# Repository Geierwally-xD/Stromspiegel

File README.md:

#LED driver 
Output driver 4 LEDs for scale lighting of models.
Layout and circuit diagram is designed with KiCad. 

4 Konstantstromquellen zum Treiben von LEDs zur Scalebeleuchtung von Modellen.

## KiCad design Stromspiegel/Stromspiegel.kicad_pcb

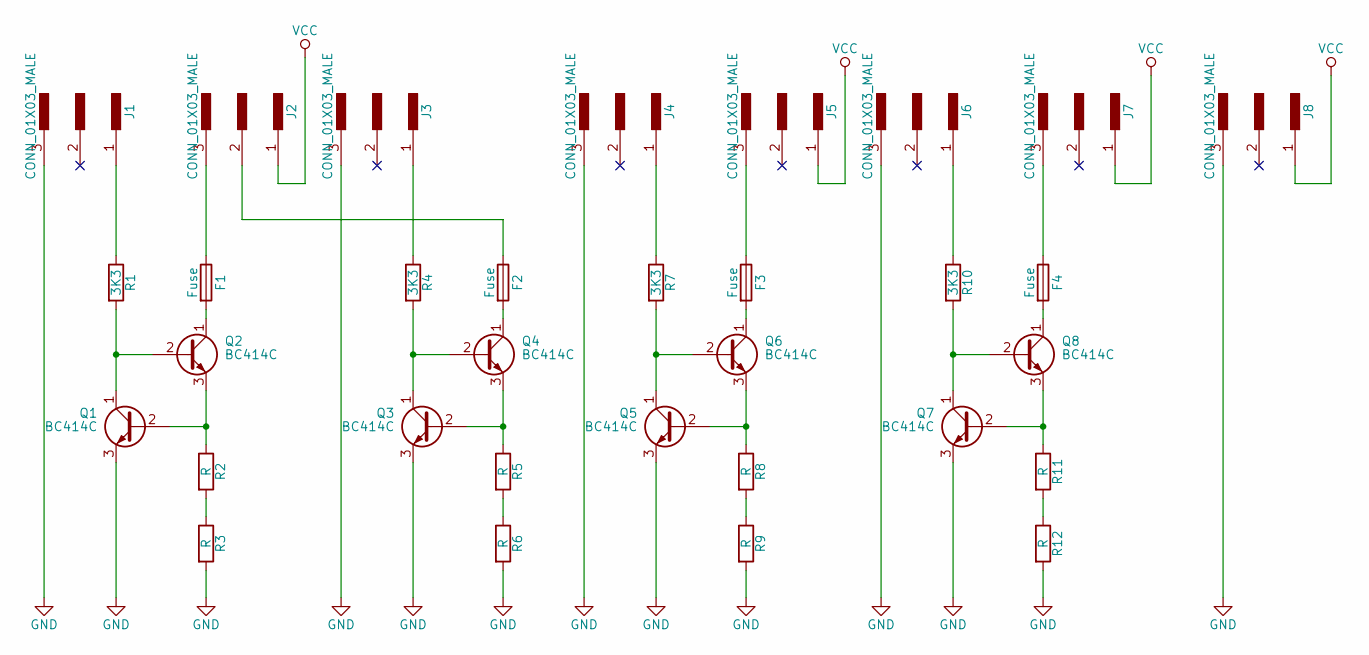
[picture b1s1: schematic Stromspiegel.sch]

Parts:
F1, F2, F3, F4: Fuse; R_Box_L8.4mm_W2.5mm_P5.08mm
J1, J2, J3, J4, J5, J6, J7, J8: CONN_01X03_MALE; Socket_Strip_Straight_1x03_Pitch2.54mm
Q1, Q2, Q3, Q4, Q5, Q6, Q7, Q8: BC414C; TO-92_Molded_Wide
R1, R4, R7, R10: 3K3; R_Axial_DIN0411_L9.9mm_D3.6mm_P15.24mm_Horizontal
R2, R3, R5, R6, R8, R9, R11, R12: R; R_Axial_DIN0411_L9.9mm_D3.6mm_P15.24mm_Horizontal

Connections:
GND: J1.3, J3.3, J4.3, J6.3, J8.3, Q1.3 (E), Q3.3 (E), Q5.3 (E), Q7.3 (E), R3.2, R6.2, R9.2, R12.2
unnamed: F1.1, J2.3
unnamed: F1.2, Q2.1 (C)
unnamed: F2.1, J2.2
unnamed: F2.2, Q4.1 (C)
unnamed: F3.1, J5.3
unnamed: F3.2, Q6.1 (C)
unnamed: F4.1, J7.3
unnamed: F4.2, Q8.1 (C)
unnamed: J1.1, R1.1
unnamed: J3.1, R4.1
unnamed: J4.1, R7.1
unnamed: J6.1, R10.1
unnamed: Q1.1 (C), Q2.2 (B), R1.2
unnamed: Q1.2 (B), Q2.3 (E), R2.1
unnamed: Q3.1 (C), Q4.2 (B), R4.2
unnamed: Q3.2 (B), Q4.3 (E), R5.1
unnamed: Q5.1 (C), Q6.2 (B), R7.2
unnamed: Q5.2 (B), Q6.3 (E), R8.1
unnamed: Q7.1 (C), Q8.2 (B), R10.2
unnamed: Q7.2 (B), Q8.3 (E), R11.1
unnamed: R2.2, R3.1
unnamed: R5.2, R6.1
unnamed: R8.2, R9.1
unnamed: R11.2, R12.1
VCC: J2.1, J5.1, J7.1, J8.1

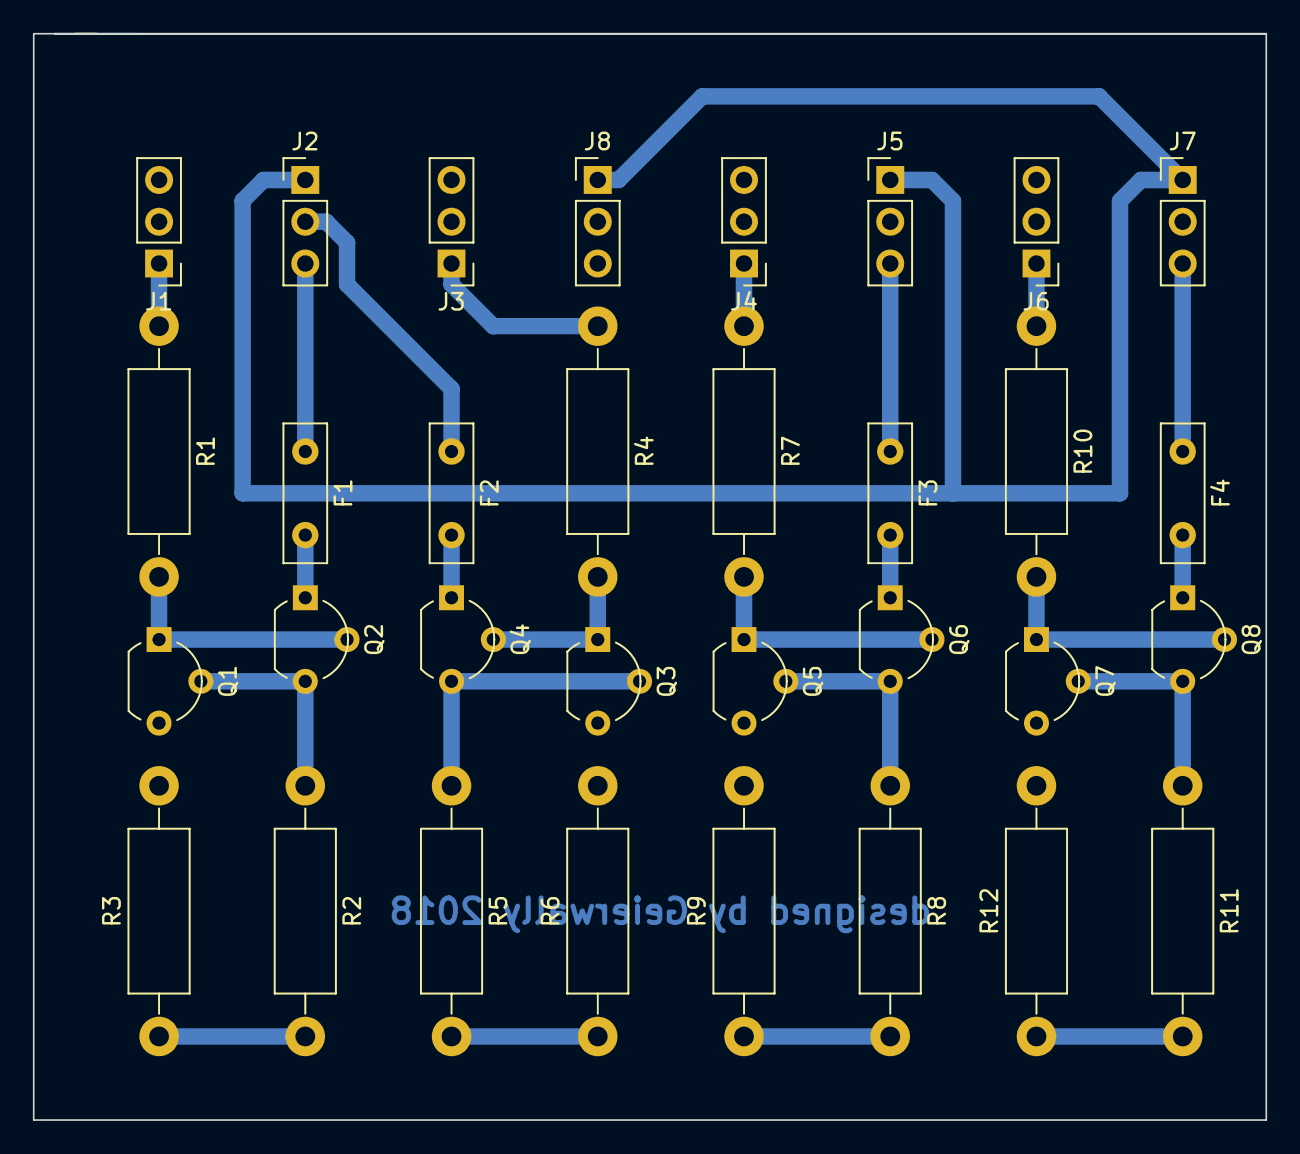
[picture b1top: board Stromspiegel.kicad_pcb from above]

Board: 2 copper layers, 74.9 x 66.0 mm, 32 parts (0 on the bottom side), 26 nets.

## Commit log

2018-02-03 images added to readme.md
